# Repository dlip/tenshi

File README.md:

# Tenshi Keyboard

- RP2040-Zero controllers
- Split using USB-C to connect the halves
- Slide-adjustable Dual Cirque 40mm trackpads
- [QMK Firmware](https://github.com/dlip/qmk_firmware/tree/dlip/keyboards/tenshi)
- Custom PCB and case
- Name from Japanese means angel (the trackpads are the halos)

## BOM

- PCBs - send the [Gerber](kicad/gerber_to_order) file to the PCB manufacturer of your choice
- 2 x RP2040-Zero
- 2 x HRO TYPE-C-31-M-12 USB C female ports
- 2 x USB-C cables
- 0-2 x Cirque 40mm Trackpads TM040040-2024-302 with flat overlay
- 0-2 x Hirose FH12-12S-0.5SH FFC/FPC connectors
- 0-2 FFC/FPC cables - 5cm length, 12 position, 0.5mm pitch, same-sided contacts
- 32 x 1N4148 SOD-123 Diodes
- 32 x kailh hotswap sockets
- 32 x low profile choc switches and keycaps
- 6 x Knurled Insert Nuts M2 x 3mm Length x 3.5mm outer diameter
- 6 x M2 4mm flat head screws
- 8 x Rubber feet

## Printables

The .stls are in the [printables](./printables) folder and there is also the [OnShape Project](https://cad.onshape.com/documents/9fc41580bdc06f2de5a54d4e/w/2ac3b2b1ad9676183a17550a/e/836a95015accbfb788e70834) in case you want to make modifications.

## Build Pics

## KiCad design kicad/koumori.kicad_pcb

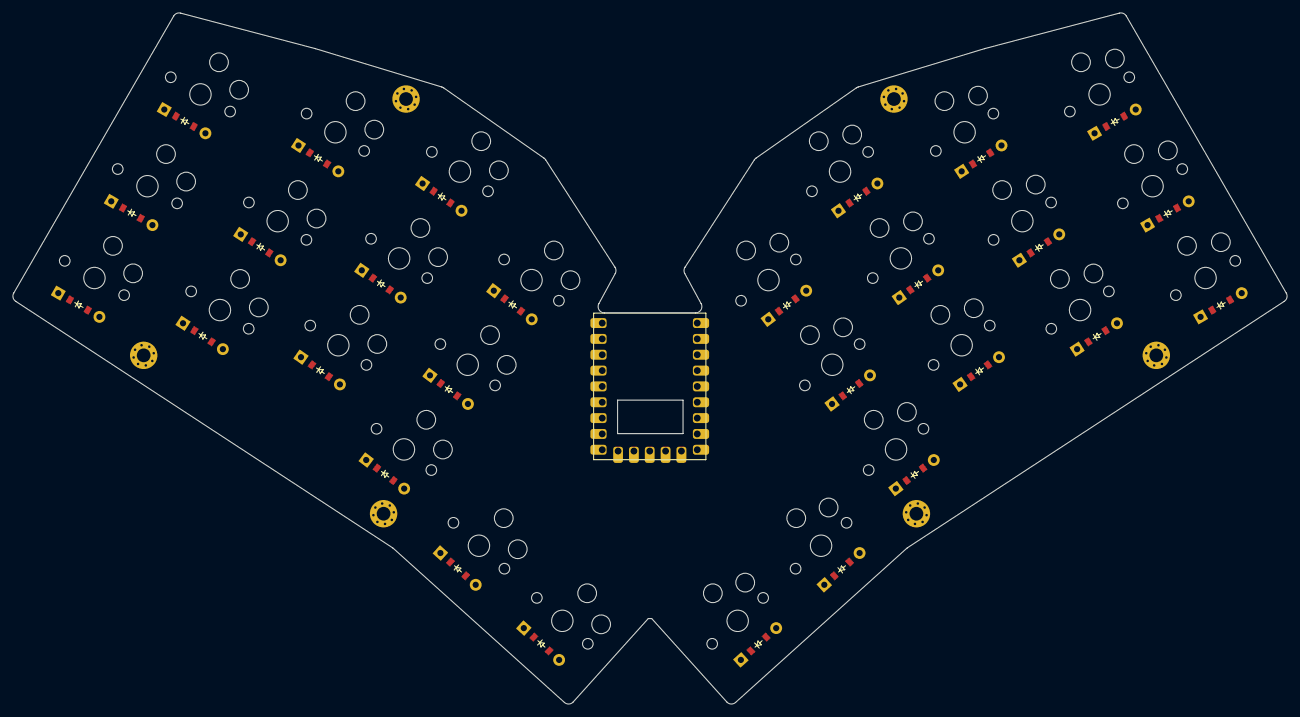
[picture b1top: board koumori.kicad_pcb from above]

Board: 2 copper layers, 204.3 x 110.8 mm, 63 parts (0 on the bottom side), 39 nets, no tracks yet.

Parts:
D1, D2, D3, D4, D5, D6, D7, D8, D9, D10, D11, D12, D13, D14, D15, D16, D17, D18, D19, D20, D21, D22, D23, D24, D25, D26, D27, D28: ComboDiode
RP2040Zero1: RP2040-Zero
S1, S2, S3, S4, S5, S6, S7, S8, S9, S10, S11, S12, S13, S14, S15, S16, S17, S18, S19, S20, S21, S22, S23, S24, S25, S26, S27, S28: PG1350
_1, _2, _3, _4, _5, _6: MountingHole_2.2mm_M2_Pad_Via

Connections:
GP0: D17.1, D20.1, D23.1, D26.1, RP2040Zero1.1
GP1: D16.1, D19.1, D22.1, D25.1, RP2040Zero1.2
GP6: D15.1, D18.1, D21.1, D24.1, RP2040Zero1.7
GP7: D13.1, D14.1, D27.1, D28.1, RP2040Zero1.8
GP10: RP2040Zero1.11, S1.1, S2.1, S3.1, S15.1, S16.1, S17.1, S27.1
GP11: RP2040Zero1.12, S4.1, S5.1, S6.1, S18.1, S19.1, S20.1, S28.1
GP12: RP2040Zero1.13, S7.1, S8.1, S9.1, S14.1, S21.1, S22.1, S23.1
GP13: RP2040Zero1.14, S10.1, S11.1, S12.1, S13.1, S24.1, S25.1, S26.1
GP27: D1.1, D4.1, D7.1, D10.1, RP2040Zero1.18
GP28: D2.1, D5.1, D8.1, D11.1, RP2040Zero1.22
GP29: D3.1, D6.1, D9.1, D12.1, RP2040Zero1.23
index_bottom: D10.2, S10.2
index_middle: D11.2, S11.2
index_top: D12.2, S12.2
inner_top: D13.2, S13.2
middle_bottom: D7.2, S7.2
middle_middle: D8.2, S8.2
middle_top: D9.2, S9.2
mirror_index_bottom: D24.2, S24.2
mirror_index_middle: D25.2, S25.2
mirror_index_top: D26.2, S26.2
mirror_inner_top: D27.2, S27.2
mirror_middle_bottom: D21.2, S21.2
mirror_middle_middle: D22.2, S22.2
mirror_middle_top: D23.2, S23.2
mirror_outer_top: D28.2, S28.2
mirror_pinky_bottom: D15.2, S15.2
mirror_pinky_middle: D16.2, S16.2
mirror_pinky_top: D17.2, S17.2
mirror_ring_bottom: D18.2, S18.2
mirror_ring_middle: D19.2, S19.2
mirror_ring_top: D20.2, S20.2
outer_top: D14.2, S14.2
pinky_bottom: D1.2, S1.2
pinky_middle: D2.2, S2.2
pinky_top: D3.2, S3.2
ring_bottom: D4.2, S4.2
ring_middle: D5.2, S5.2
ring_top: D6.2, S6.2

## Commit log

2024-07-13 Add files
2024-07-13 Add bom
2024-07-13 Add logo
2024-07-13 Add url
2024-07-13 change fill
2024-07-13 Add gerbers
2024-07-25 Add printables
2024-07-25 Add build pics
2024-07-25 Fix images
2024-07-25 typo
2024-07-25 Qmk link
2024-07-30 Add support to trackpad
2026-01-15 Add rufous
2026-01-15 Center
2026-01-15 compact
